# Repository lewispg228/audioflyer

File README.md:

# audioflyer
Surround sound audio mixing controlled by serial commands. Making mixes that fly!

Why? Because this is going to be awesome.

The plan is to use a SparkFun Tsunami Wav Trigger board to play lots of audio files. To start off, I plan to use some tasty guitar riffs and various reverbs/effects. Maybe bass, drums and vocals. We shall see. Then play these tracks through a set of 8 speakers arranged in something similar to 7.1 surround.

For amplification, I am using four SparkFun Audio Amps. They are stereo amps, so this will get me 8 channels.

I hope to start many tracks at the same time, and then control their volume in all 8 tracks with serial commands from a micro controller - probably an arduino. I love the idea of using some code to pull off some smooth motions, spatial movements, rotation of the entire mix around my head, "fly by" guitar solos, and even some volume tricks that may be close to impossible to pull off with manual moving of faders, and a big pain to draw in on automation control tracks. This could mean that I want the snare to spin around my head every time I hit it. It might prove to be annoying, but it might also be totally awesome! What about using the random function in arduino to place where each instrument will live for each mix - it means that every listening experience would be unique - pretty F-in' cool if you ask me.

What got me turned onto this idea was binaural recordings. It's basically a technique that's been around for a long time where you put tiny microphones in your ears (facing outward) or you put them on a dummy head, and then record both mics. When you listen to them back on headphones, you can really hear the position of all the sounds. I guess it has something to do with how our brains calculate time differences and bass roll off difference between each ear. Wild stuff! I bought a pair of these mics from The Sound Professionals for 79 bucks and they sound amazing! I can't wait to track some crazy surround sound mixes and then be able to listen back on headphones anywhere and hear the awesome spatial automation.

This has bound to have been done before... but maybe not? I'm not interested in just rocking 5.1 or 7.1 surround mixes with fancy sound cards and cool plugins. I want to control the entire mix from code on a micro. This will open the door to new sound movement effects that I can't even predict at this time.

All I need is volume control for each track to each output. From reading about the Tsunami, it sounds like this is very possible.

How hard can it be?

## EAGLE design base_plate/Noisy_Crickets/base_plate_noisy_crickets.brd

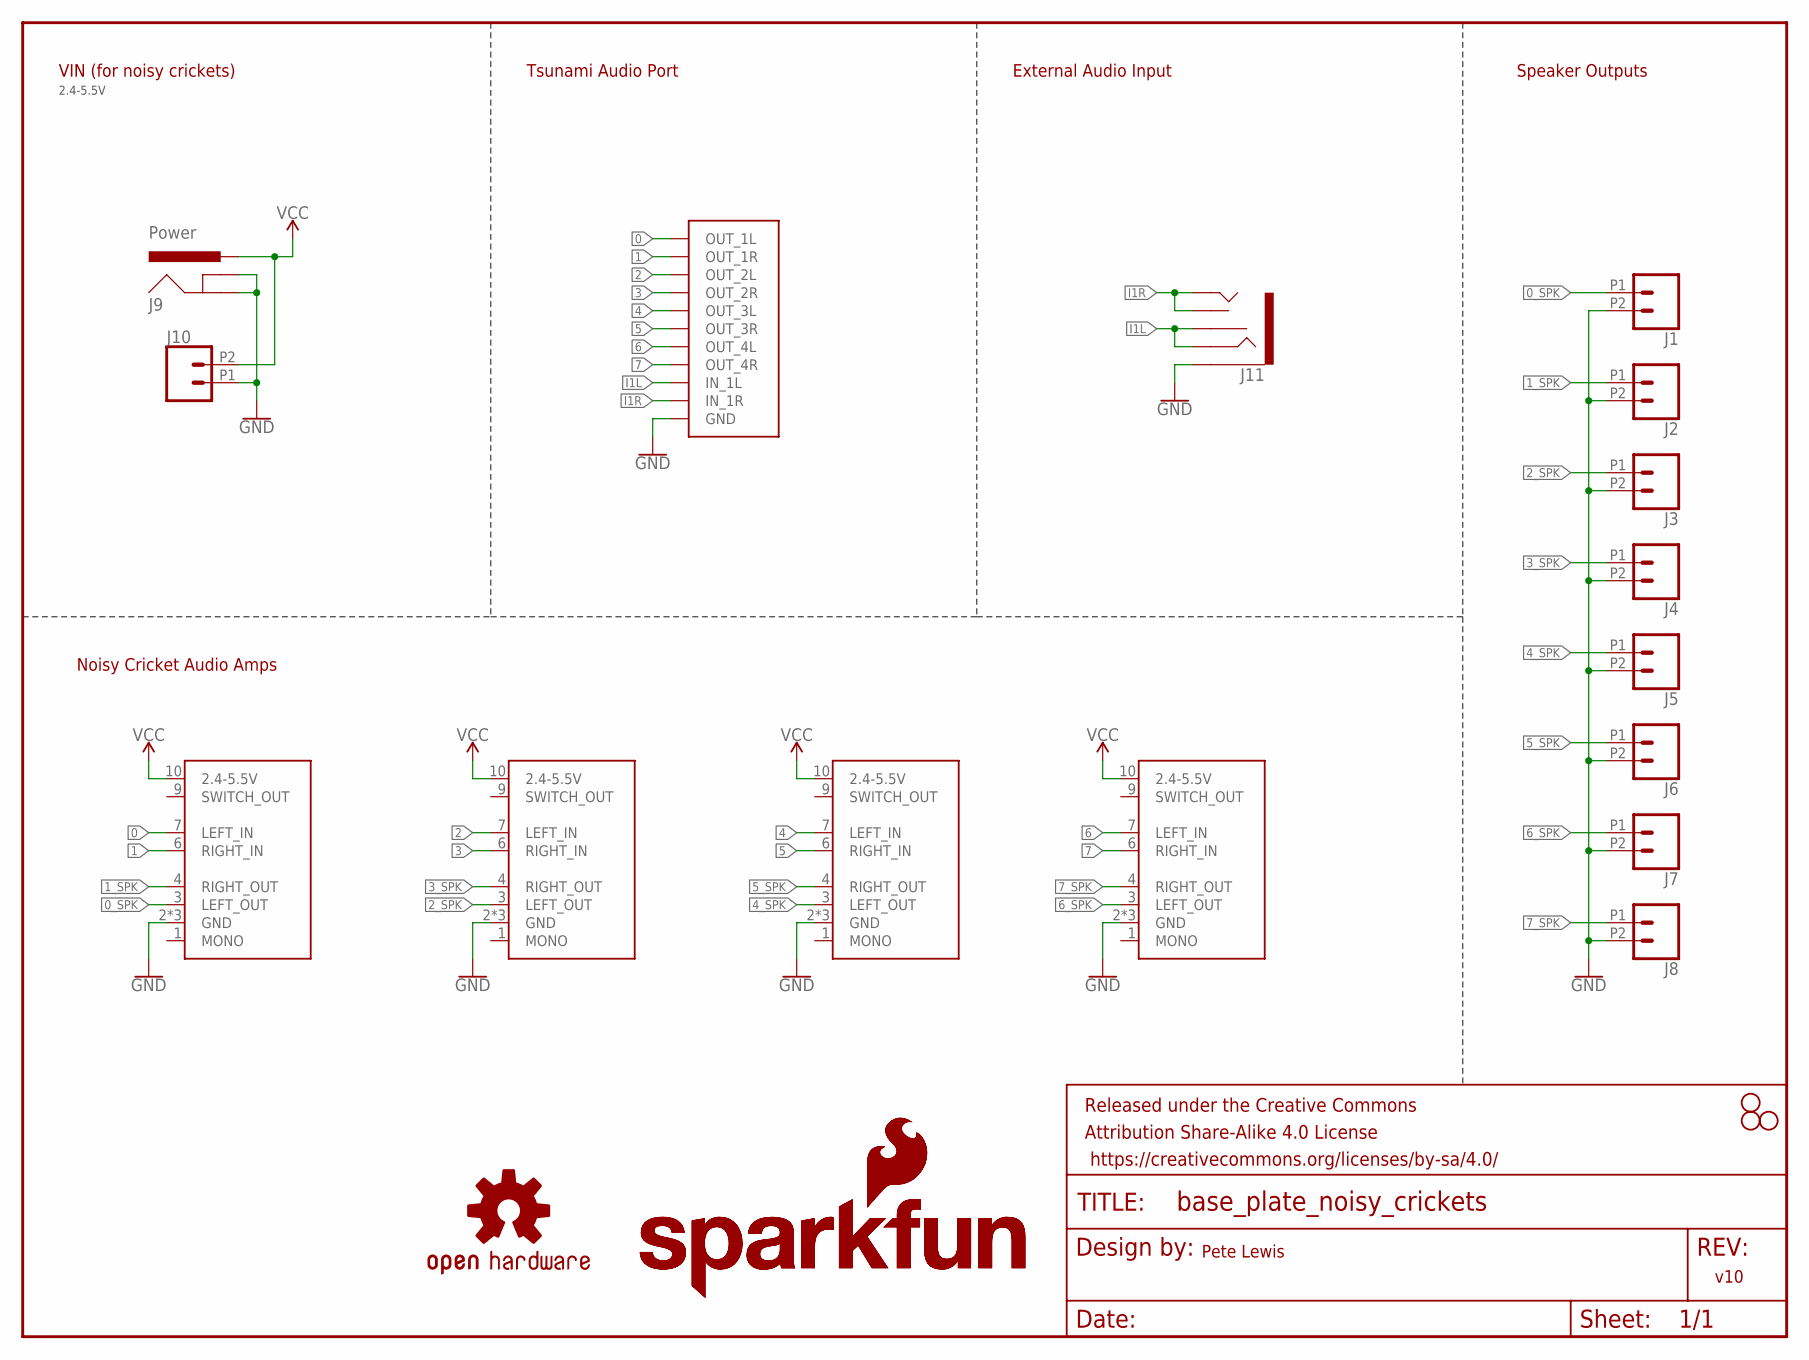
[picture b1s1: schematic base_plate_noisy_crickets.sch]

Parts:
FRAME1: FRAME-LETTER; CREATIVE_COMMONS
H1, H3, H4: STAND-OFFTIGHT; STAND-OFF-TIGHT
J1, J2, J3, J4, J5, J6, J7, J8, J10: CONN_022.54MM_SCREWTERM; 1X02_2.54_SCREWTERM
J9: Power; POWER_JACK_PTH_LOCK
J11: AUDIO_JACK_3.5MM_PTH; AUDIO-JACK
LOGO1: SFE_LOGO_NAME_FLAME.1_INCH; SFE_LOGO_NAME_FLAME_.1
LOGO2: OSHW-LOGOS; OSHW-LOGO-S
LOGO3: SFE_LOGO_NAME_FLAME.3_INCH; SFE_LOGO_NAME_FLAME_.3
U$1, U$2, U$3, U$4: NOISY_CRICKET; NOISY_CRICKET_W_PTH
U$5: TSUNAMI_AUDIO_PORTS

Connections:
0: U$1.7 (LEFT_IN), U$5.O1L (OUT_1L)
0_SPK: J1.P1 (1), U$1.3 (LEFT_OUT)
1: U$1.6 (RIGHT_IN), U$5.O1R (OUT_1R)
1_SPK: J2.P1 (1), U$1.4 (RIGHT_OUT)
2: U$2.7 (LEFT_IN), U$5.O2L (OUT_2L)
2_SPK: J3.P1 (1), U$2.3 (LEFT_OUT)
3: U$2.6 (RIGHT_IN), U$5.O2R (OUT_2R)
3_SPK: J4.P1 (1), U$2.4 (RIGHT_OUT)
4: U$3.7 (LEFT_IN), U$5.O3L (OUT_3L)
4_SPK: J5.P1 (1), U$3.3 (LEFT_OUT)
5: U$3.6 (RIGHT_IN), U$5.O3R (OUT_3R)
5_SPK: J6.P1 (1), U$3.4 (RIGHT_OUT)
6: U$4.7 (LEFT_IN), U$5.O4L (OUT_4L)
6_SPK: J7.P1 (1), U$4.3 (LEFT_OUT)
7: U$4.6 (RIGHT_IN), U$5.O4R (OUT_4R)
7_SPK: J8.P1 (1), U$4.4 (RIGHT_OUT)
GND: J1.P2 (2), J2.P2 (2), J3.P2 (2), J4.P2 (2), J5.P2 (2), J6.P2 (2), J7.P2 (2), J8.P2 (2), J9.GND, J9.GNDBREAK, J10.P1 (1), J11.SLEEVE, U$1.2 (GND), U$1.5 (GND), U$1.8 (GND), U$2.2 (GND), U$2.5 (GND), U$2.8 (GND), U$3.2 (GND), U$3.5 (GND), U$3.8 (GND), U$4.2 (GND), U$4.5 (GND), U$4.8 (GND), U$5.P$11 (GND), U$5.P$12 (GND), U$5.P$13 (GND), U$5.P$14 (GND), U$5.P$15 (GND), U$5.P$16 (GND), U$5.P$17 (GND), U$5.P$18 (GND), U$5.P$19 (GND), U$5.P$20 (GND)
I1L: J11.RING, J11.RSH, U$5.I1L (IN_1L)
I1R: J11.TIP, J11.TSH, U$5.I1R (IN_1R)
VCC: J9.PWR, J10.P2 (2), U$1.10 (2.4-5.5V), U$2.10 (2.4-5.5V), U$3.10 (2.4-5.5V), U$4.10 (2.4-5.5V)

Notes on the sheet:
Speaker Outputs
Noisy Cricket Audio Amps
VIN (for noisy crickets)
Tsunami Audio Port
External Audio Input
2.4-5.5V
Pete Lewis
v10

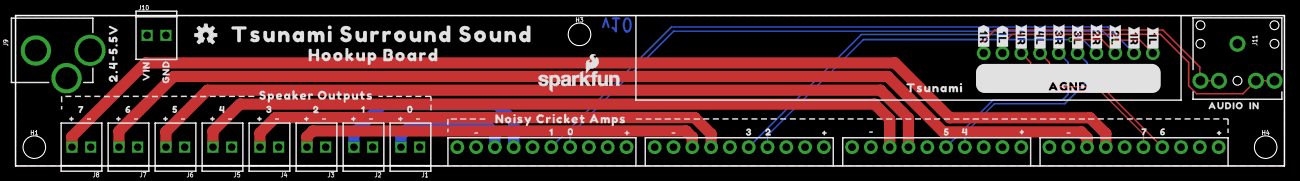
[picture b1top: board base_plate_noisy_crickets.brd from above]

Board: 2 copper layers, 171.5 x 20.3 mm, 87 parts (1 on the bottom side), 20 nets.

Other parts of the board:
E$6: REDBOARD_ARTEMIS
E$8: THING_PLUS
U$6: AUDIO0
U$7: IN0
U$8, U$57: 00
U$9, U$58: 10
U$10, U$59: 20
U$11, U$60: 30
U$12, U$61: 40
U$13, U$62: 50
U$14, U$63: 60
U$15, U$64: 70
U$16, U$17, U$18, U$19, U$20, U$21, U$22, U$23, U$49, U$50, U$51, U$52: #0
U$24, U$25, U$26, U$27, U$28, U$29, U$30, U$32, U$48, U$53, U$54, U$55: #_0
U$31: VIN0
U$33: GND0
U$34: TSUNAMI_SURROUND_SOUND0
U$35: HOOKUP_BOARD0
U$36: 2#4#5#5V0
U$37: #AGND#0
U$38: #1R#0
U$39: #2L#0
U$40: #2R#0
U$41: #3R#0
U$42: #3L#0
U$43: #4L#0
U$44: #4R#0
U$45: #1L#0
U$46: NOISY_CRICKET_AMPS0
U$47: TSUNAMI0
U$56: SPEAKER_OUTPUTS0
U$65: TSUNAMI
U$116: #1L#3
U$164: #1R#3

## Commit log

2018-02-27 pic of amps and baseplate layout
2018-02-27 updating readme - the initial mission
2018-02-27 audio flyer
2018-02-27 audio flyer
    i like this name better
2018-03-05 tweaked base plate and exported to dxf
2018-03-14 some stuff I really aught to try
2018-03-14 more wacky ideas
2018-03-20 got some audio playing from arduino example wahoo!!
    still no luck with python attempt, but at least I know that my hardware
    is working.
    Also tried out some reverb ideas, but it didn't realy sound that good.
    I'm wondering if some of the dry track needs to be in the reverb tracks
    too.
2019-05-01 including MOB testing sketch and some other minor delay tweaks
2022-10-27 4 on the floor example and base plate design

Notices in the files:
parts and their libraries:
SparkFun-Connectors: Licensing: Creative Commons ShareAlike 4.0 International - https://creativecommons.org/licenses/by-sa/4.0
SparkFun-Aesthetics: Released under the Creative Commons Attribution Share-Alike 4.0 License
SparkFun-Aesthetics: https://creativecommons.org/licenses/by-sa/4.0
